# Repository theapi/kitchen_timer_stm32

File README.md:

# kitchen_timer_stm32
A kitchen timer using the Arm STM32

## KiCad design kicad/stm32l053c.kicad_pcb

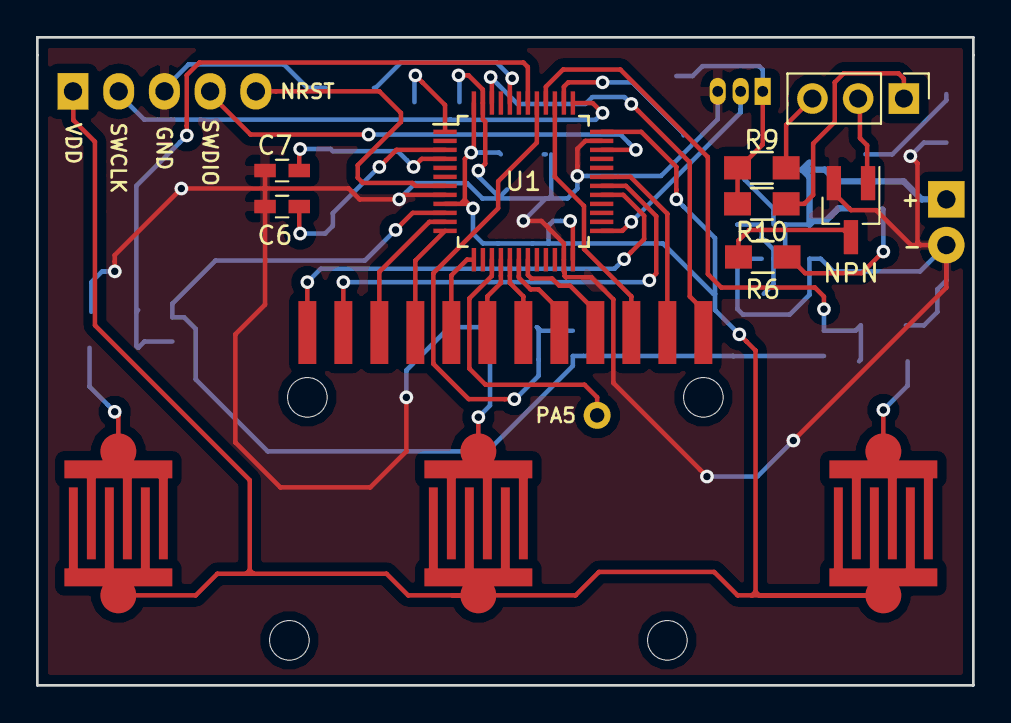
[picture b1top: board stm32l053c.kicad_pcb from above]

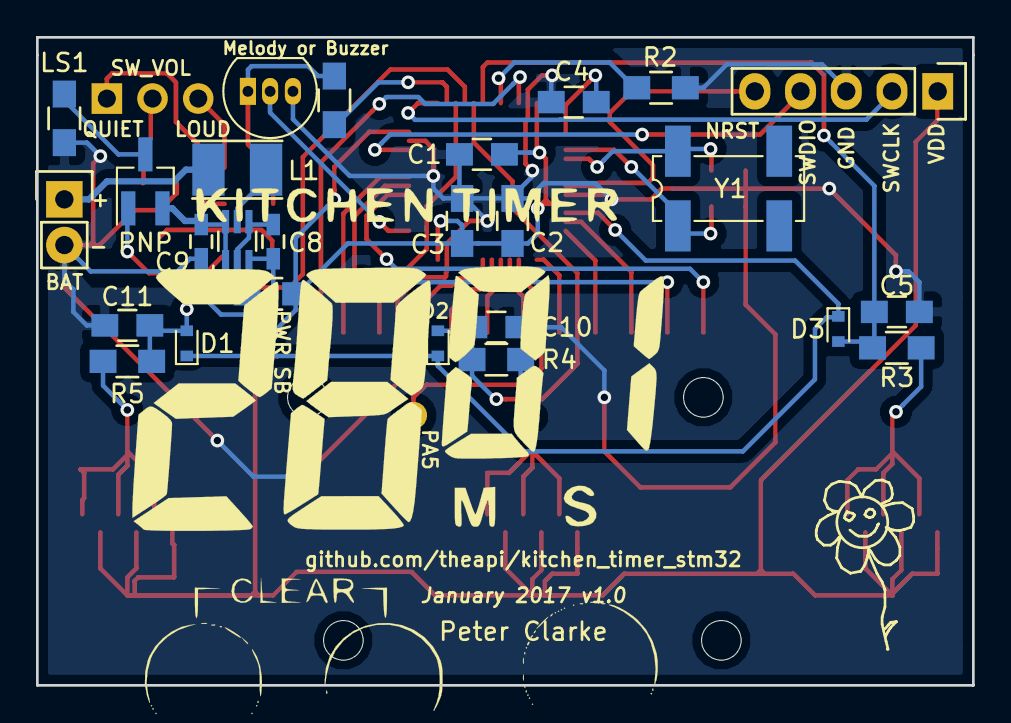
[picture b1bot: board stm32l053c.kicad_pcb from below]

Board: 2 copper layers, 52.0 x 36.0 mm, 39 parts (26 on the bottom side), 41 nets.

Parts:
BAT: PWR; Pin_Header_Straight_1x02
C1, C2, C3, C4, C5, C10, C11: 100nF; C_0805_HandSoldering
C6, C7: 4.3pF; C_0603_HandSoldering
C8, C9: 10uF; C_0603_HandSoldering
D1, D2, D3: D_Schottky; SOD-523
DS1: LCD_KITCHEN_TIMER; ZEBRA-12
L1: INDUCTOR; Inductor_Taiyo-Yuden_NR-30xx_HandSoldering
LS1: BUZZER; R_0805_HandSoldering
Melody or Buzzer: 0; R_0805_HandSoldering
NPN: BC817; SOT-23_Handsoldering
P1: SWD; Pin_Header_Straight_1x05
PA5: TEST_1P; Measurement_Point_Round-TH_Small
PNP: BC807; SOT-23_Handsoldering
PWR SB: 0; R_0805_HandSoldering
R2: 10K; R_0805_HandSoldering
R3, R4, R5: 1K; R_0805_HandSoldering
R6, R9: 220; R_0805_HandSoldering
R10: 2K2; R_0805_HandSoldering
SW1, SW2, SW3: SW_PUSH; SW_PCB
SW_VOL: SW_SPDT; Pin_Header_Straight_1x03_Pitch2.54mm
U1: STM32L053C8_LQFP48; LQFP-48_7x7mm_Pitch0.5mm
U2: TLV61225; SC-70-6
U3: um66t; UM66T_MELODY
Y1: Crystal_GND23; Crystal_SMD_SeikoEpson_MC306-4pin_8.0x3.2mm_HandSoldering

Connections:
+BATT: BAT.1, C9.1, L1.1, PNP.2, U2.1, U2.6
/BUTTON0: C11.1, D1.2, R5.1, U1.40
/BUTTON1: C10.1, D2.2, R4.1, U1.41
/BUTTON2: C5.1, D3.2, R3.1, U1.42
/BUZZER: Melody or Buzzer.2, U1.38
/LCD_COM0: DS1.1, U1.29
/LCD_COM1: DS1.2, U1.30
/LCD_COM2: DS1.11, U1.31
/LCD_COM3: DS1.12, U1.46
/LCD_SEG0: DS1.3, U1.11
/LCD_SEG1: DS1.4, U1.12
/LCD_SEG2: DS1.5, U1.13
/LCD_SEG3: DS1.6, U1.16
/LCD_SEG4: DS1.7, U1.17
/LCD_SEG5: DS1.8, U1.18
/LCD_SEG6: DS1.9, U1.19
/LCD_SEG7: DS1.10, U1.39
/MELODY: U1.25, U3.2
/NPN_BASE: NPN.1, SW_VOL.2
/OSC32_IN: C6.1, U1.3, Y1.1
/OSC32_OUT: C7.1, U1.4, Y1.4
/PNP_BASE: PNP.1, R6.2
/VLCD: C4.2, U1.1
/WAKEUP_PIN1: D1.1, D2.1, D3.1, U1.10
Earth: BAT.2, C1.2, C2.2, C3.2, C4.1, C5.2, C6.2, C7.2, C8.2, C9.2, C10.2, C11.2, LS1.2, NPN.2, P1.3, R2.2, U1.8, U1.23, U1.35, U1.47, U2.3, U3.3
NRST: P1.5, U1.7
unnamed: C8.1, PWR SB.2, U2.2, U2.4
unnamed: L1.2, U2.5
unnamed: LS1.1, PNP.3
unnamed: NPN.3, R6.1
unnamed: Melody or Buzzer.1, R9.1, R10.1, U3.1
unnamed: R2.1, U1.44
unnamed: R3.2, SW1.2
unnamed: R4.2, SW2.2
unnamed: R5.2, SW3.2
unnamed: R9.2, SW_VOL.3
unnamed: R10.2, SW_VOL.1
unnamed: PA5.1, U1.15
SWCLK: P1.2, U1.37
SWDIO: P1.4, U1.34
VDD: C1.1, C2.1, C3.1, P1.1, PWR SB.1, SW1.1, SW2.1, SW3.1, U1.9, U1.24, U1.36, U1.48

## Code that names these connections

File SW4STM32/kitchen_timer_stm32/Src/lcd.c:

/**
 * @file LCD.c
 * Description: This file provides code for the configuration
 *    of the LCD instances.
 */

#include "lcd.h"
#include "gpio.h"

LCD_HandleTypeDef hlcd;

/* LCD init function 64Hz */
void MX_LCD_Init(void) {

    hlcd.Instance = LCD;
    hlcd.Init.Prescaler = LCD_PRESCALER_4;
    hlcd.Init.Divider = LCD_DIVIDER_16;
    hlcd.Init.Duty = LCD_DUTY_1_4;
    hlcd.Init.Bias = LCD_BIAS_1_4;
    hlcd.Init.VoltageSource = LCD_VOLTAGESOURCE_INTERNAL;
    hlcd.Init.Contrast = LCD_CONTRASTLEVEL_7;
    hlcd.Init.DeadTime = LCD_DEADTIME_1;
    hlcd.Init.PulseOnDuration = LCD_PULSEONDURATION_1;
    hlcd.Init.HighDrive = LCD_HIGHDRIVE_1;
    hlcd.Init.BlinkMode = LCD_BLINKMODE_OFF;
    hlcd.Init.BlinkFrequency = LCD_BLINKFREQUENCY_DIV8;
    hlcd.Init.MuxSegment = LCD_MUXSEGMENT_DISABLE;
    if (HAL_LCD_Init(&hlcd) != HAL_OK) {
        Error_Handler();
    }

    /**Enable the High Driver 
     */
    __HAL_LCD_HIGHDRIVER_ENABLE(&hlcd);

}

void HAL_LCD_MspInit(LCD_HandleTypeDef* lcdHandle) {

    GPIO_InitTypeDef GPIO_InitStruct;
    if (lcdHandle->Instance == LCD) {
        /* USER CODE BEGIN LCD_MspInit 0 */

        /* USER CODE END LCD_MspInit 0 */
        /* Peripheral clock enable */
        __HAL_RCC_LCD_CLK_ENABLE();

        /**LCD GPIO Configuration
         PA1     ------> LCD_SEG0
         PA2     ------> LCD_SEG1
         PA3     ------> LCD_SEG2
         PA6     ------> LCD_SEG3
         PA7     ------> LCD_SEG4
         PB0     ------> LCD_SEG5
         PB1     ------> LCD_SEG6
         PA8     ------> LCD_COM0
         PA9     ------> LCD_COM1
         PA10     ------> LCD_COM2
         PB3     ------> LCD_SEG7
         PB9     ------> LCD_COM3
         */
        GPIO_InitStruct.Pin = GPIO_PIN_1 | GPIO_PIN_2 | GPIO_PIN_3 | GPIO_PIN_6
                | GPIO_PIN_7 | GPIO_PIN_8 | GPIO_PIN_9 | GPIO_PIN_10;
        GPIO_InitStruct.Mode = GPIO_MODE_AF_PP;
        GPIO_InitStruct.Pull = GPIO_NOPULL;
        GPIO_InitStruct.Speed = GPIO_SPEED_FREQ_LOW;
        GPIO_InitStruct.Alternate = GPIO_AF1_LCD;
        HAL_GPIO_Init(GPIOA, &GPIO_InitStruct);

        GPIO_InitStruct.Pin = GPIO_PIN_0 | GPIO_PIN_1 | GPIO_PIN_3 | GPIO_PIN_9;
        GPIO_InitStruct.Mode = GPIO_MODE_AF_PP;
        GPIO_InitStruct.Pull = GPIO_NOPULL;
        GPIO_InitStruct.Speed = GPIO_SPEED_FREQ_LOW;
        GPIO_InitStruct.Alternate = GPIO_AF1_LCD;
        HAL_GPIO_Init(GPIOB, &GPIO_InitStruct);

        /* USER CODE BEGIN LCD_MspInit 1 */

        /* USER CODE END LCD_MspInit 1 */
    }
}

void HAL_LCD_MspDeInit(LCD_HandleTypeDef* lcdHandle) {

    if (lcdHandle->Instance == LCD) {
        /* USER CODE BEGIN LCD_MspDeInit 0 */

        /* USER CODE END LCD_MspDeInit 0 */
        /* Peripheral clock disable */
        __HAL_RCC_LCD_CLK_DISABLE();

        /**LCD GPIO Configuration
         PA1     ------> LCD_SEG0
         PA2     ------> LCD_SEG1
         PA3     ------> LCD_SEG2
         PA6     ------> LCD_SEG3
         PA7     ------> LCD_SEG4
         PB0     ------> LCD_SEG5
         PB1     ------> LCD_SEG6
         PA8     ------> LCD_COM0
         PA9     ------> LCD_COM1
         PA10     ------> LCD_COM2
         PB3     ------> LCD_SEG7
         PB9     ------> LCD_COM3
         */
        HAL_GPIO_DeInit(GPIOA,
                GPIO_PIN_1 | GPIO_PIN_2 | GPIO_PIN_3 | GPIO_PIN_6 | GPIO_PIN_7
                        | GPIO_PIN_8 | GPIO_PIN_9 | GPIO_PIN_10);

        HAL_GPIO_DeInit(GPIOB,
                GPIO_PIN_0 | GPIO_PIN_1 | GPIO_PIN_3 | GPIO_PIN_9);

    }

}

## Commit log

2016-12-11 Start of schematic
2016-12-12 Updated footprint
2016-12-12 LCD footprint
2016-12-12 LCD connections
2016-12-12 Power supply
2016-12-13 Buttons
2016-12-14 Button debounce
2016-12-14 Buzzer
2016-12-15 Some footprints
2016-12-17 Mosfet to drive the buzzer
2016-12-19 Footprints for buttons & zebra
2016-12-19 Initial layout
2016-12-19 Changing the pcb button
2016-12-19 Fixed the pcb buttons
2016-12-19 Enclosure sizes
2016-12-19 Layout to fit the enclosure
2016-12-21 Initial code import
2016-12-22 Time set & countdown
2016-12-22 Turn off RTC when alarm is on
2016-12-22 Handle buttons in a state machine
2016-12-23 Change the systick interrupt to not wake up every millisecond
2016-12-23 Disable the systick interrupt to not wake up every millisecond
2016-12-23 ensure that the WUF wakeup flag is cleared.
2016-12-24 HAL_PWR_EnterSTANDBYMode()
2016-12-26 Long press to change the time setting faster
2016-12-26 If nothing has happened for a while, turn off.
2016-12-27 Continuos loop when setting the time
2016-12-27 Remember the set time
2016-12-30 Datasheet for the buzzer transistor
2016-12-30 Datasheet for the buzzer transistor Farnell equivelent
2017-01-01 62 ms pulses of 2048Hz for the buzzer alarm
2017-01-01 alarm triggered pin
2017-01-01 STATE_RESET
2017-01-01 Schematic pdf
2017-01-01 Blink the display while the alarm sounds
2017-01-01 EEPROM in seperate files
2017-01-01 Stop the alarm with the ST/SP button
2017-01-02 Buzzer or Melody
2017-01-02 NCP1400A as a possible boost converter
2017-01-02 boost regulator docs
2017-01-02 Updated schematic pdf
2017-01-02 Layout (WIP)
2017-01-02 Moved the melody pin
2017-01-02 Fixed the melody output
2017-01-02 Stop noise on the buzzer
2017-01-02 Pull down on the buzzer transistor
2017-01-02 Moved the docs
2017-01-03 Buzzer transistor to be decided
2017-01-03 BC817 transistor
2017-01-03 PNP & more layout
2017-01-03 Re-wired the zebra strip
2017-01-08 Naming convention
2017-01-08 KT struct rather than global variables
2017-01-09 Moving to state machine struct (WIP)
2017-01-09 Using some state functions
2017-01-09 Changed KT_IdleTimeout() to return 1 on timeout
2017-01-09 Alarm states in functions too
2017-01-10 Moved the kitchen timer state into the kt struct
2017-01-10 Moved the main state machine into its own function
2017-01-10 The NPN is needed to completely disconnect the buzzer, otherwise it continually uses power
2017-01-10 Moved button handling to separate files
2017-01-11 check for & handle a button interrupt before sleeping
2017-01-12 4.3pF caps on the crystal as in the Nucleo board
2017-01-14 Save a byte with flash wear protection
2017-01-14 Removed output.map from the repo
2017-01-14 Initialize the epprom counters
2017-01-14 Removed old comment
2017-01-15 Simpler to use a separate word for both counter & data
2017-01-15 Speed up the setting is the button is held longer
2017-01-15 Crystal & melody footprints
2017-01-16 Bottom initial routing
2017-01-17 Moved the MCU to the top of the board
2017-01-17 Init buttons & output button pressed to PA5
2017-01-17 Moved the buzzer pin to a more convenient location
2017-01-17 Layout
2017-01-18 Power supply connections
2017-01-18 All connected & DRC pass
2017-01-18 Image of the readout on the pcb
2017-01-19 Boost converted on separate ground
2017-01-19 Hand solder friendly footprint for the boost regulator
2017-01-20 Crystal datasheet
2017-01-20 Labels
2017-01-23 Cropped hero silkscreen
2017-01-23 Routing tweeks
2017-01-23 kerbers
2017-02-12 Corrected the labels for the button R/C
2017-02-13 Swap LCD ram registers
2017-02-17 Debugging the buzzer
2017-03-17 Basic EEPROM minutes storage
2017-03-18 Flashed both timers
